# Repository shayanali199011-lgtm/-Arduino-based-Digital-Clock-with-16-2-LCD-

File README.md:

# -Arduino-based-Digital-Clock-with-16-2-LCD-
This project demonstrates how to design a basic Arduino Uno circuit in Eagle and program it to work as a digital clock. The time (hour:minute) is displayed on a 16×2 LCD. Users can set the time using push buttons.

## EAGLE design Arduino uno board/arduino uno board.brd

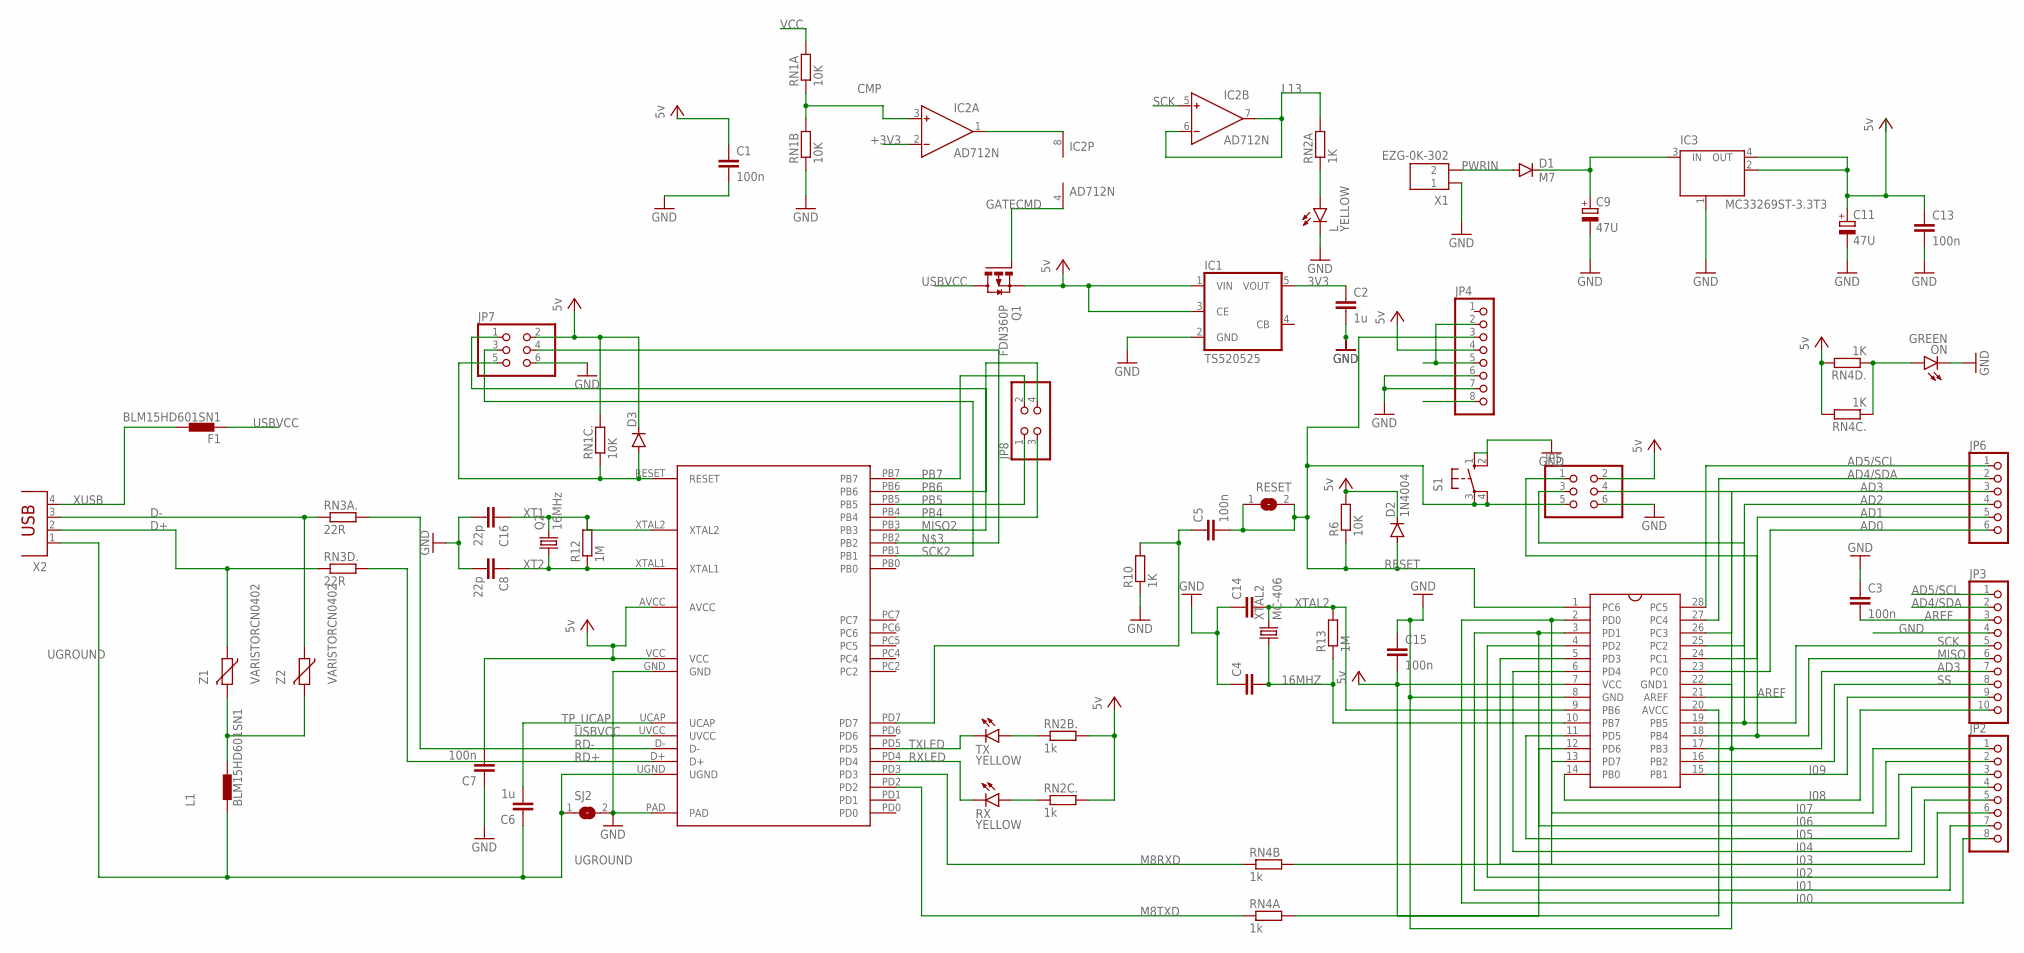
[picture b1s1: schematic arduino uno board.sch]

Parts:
C1, C3, C5, C7, C13, C15: 100n; C0603
C2, C6: 1u; C0603
C4, C14: C-EUC0603; C0603
C8, C16: 22p; C0603
C9, C11: 47U; R/2012-12W
D1: M7; MICROMELF-R
D2: 1N4004; MICROMELF-R
D3: DIODE-MICROMELF-R; MICROMELF-R
F1: BLM15HD601SN1; 0402
IC1: TS520525; SOT25
IC2: AD712N; DIL08
IC3: MC33269ST-3.3T3; SOT223
JP2, JP4: PINHD-1X8; 1X08
JP3: PINHD-1X10; 1X10
JP5, JP7: PINHD-2X3; 2X03
JP6: PINHD-1X6; 1X06
JP8: PINHD-2X2; 2X02
L: YELLOW; CHIPLED-0603-TTW
L1: BLM15HD601SN1; 0402
ON: GREEN; CHIPLED-0603-TTW
Q1: FDN360P; SUPER-SOT3
Q2: 16MHz; CTS406
R6: 10K; R0201
R10: 1K; R0201
R12, R13: 1M; R0201
RESET: SJ
RN1A, RN1B, RN1C.: 10K; R0201
RN2A, RN4C., RN4D.: 1K; R0201
RN2B., RN2C., RN4A, RN4B: 1k; R0201
RN3A., RN3D.: 22R; R0201
RX: YELLOW; CHIPLED-0603-TTW
S1: 10-XX; B3F-10XX
SJ2: SJ
TX: YELLOW; CHIPLED-0603-TTW
U$1: ARDUINOUNO
U$2: ATMEGA16U2
X1: EZG-0K-302; EZG-0B-0K-302
X2: PN61729
XTAL2: MC-406
Z1, Z2: VARISTORCN0402; CT/CN0402

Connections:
3V3: C2.1, IC1.5 (VOUT)
16MHZ: C4.2, R13.1, U$1.10 (PB7), XTAL2.1
+3V3: IC2.2 (IN-)
AD0: JP6.6, U$1.23 (PC0)
AD1: JP6.5, U$1.24 (PC1)
AD2: JP6.4, U$1.25 (PC2)
AD3: JP3.7, JP5.4, JP6.3, U$1.17 (PB3), U$1.26 (PC3)
AD4/SDA: JP3.2, JP6.2, U$1.27 (PC4)
AD5/SCL: JP3.1, JP6.1, U$1.28 (PC5)
AREF: C3.2, JP3.3, U$1.21 (AREF)
CMP: IC2.3 (IN+), RN1A.1, RN1B.2
D+: RN3D..1, X2.2, Z1.1
D-: RN3A..1, X2.3, Z2.1
GATECMD: IC2.4 (V-), Q1.1 (G)
GND: C1.2, C2.2, C3.1, C4.1, C7.1, C8.2, C9.-, C11.-, C13.2, C14.1, C15.1, C16.2, IC1.2 (GND), IC3.1 (GND/ADJ), JP3.4, JP4.6, JP4.7, JP5.6, JP7.6, L.C@1 (C), ON.C@1 (C), R10.1, RN1B.1, S1.1 (S), S1.2 (S1), SJ2.2, U$1.8 (GND), U$1.22 (GND1), U$2.GND, U$2.PAD, X1.1
I00: JP2.8, RN4B.2, U$1.2 (PD0)
I01: JP2.7, RN4A.2, U$1.3 (PD1)
I02: JP2.6, U$1.4 (PD2)
I03: JP2.5, U$1.5 (PD3)
I04: JP2.4, U$1.6 (PD4)
I05: JP2.3, U$1.11 (PD5)
I06: JP2.2, U$1.12 (PD6)
I07: JP2.1, U$1.13 (PD7)
I08: JP3.10, U$1.14 (PB0)
I09: JP3.9, U$1.15 (PB1)
L13: IC2.6 (IN-), IC2.7 (OUT), RN2A.2
M8RXD: RN4B.1, U$2.PD3
M8TXD: RN4A.1, U$2.PD2
MISO: JP3.6, JP5.1, U$1.18 (PB4)
MISO2: JP7.1, U$2.PB3
unnamed: RN2B..1, TX.A@1 (A)
unnamed: RN2C..1, RX.A@1 (A)
unnamed: JP7.4, U$2.PB2
unnamed: IC2.1 (OUT), IC2.8 (V+)
unnamed: C9.+, D1.C, IC3.3 (IN)
unnamed: L.A@1 (A), RN2A.1
unnamed: ON.A@1 (A), RN4C..1, RN4D..1
unnamed: C5.1, R10.2, U$2.PD7
unnamed: JP4.2, JP4.5
unnamed: D3.A, JP7.5, RN1C..1, U$2.RESET
unnamed: L1.2, Z1.2, Z2.2
PB4: JP8.3, U$2.PB4
PB5: JP8.1, U$2.PB5
PB6: JP8.4, U$2.PB6
PB7: JP8.2, U$2.PB7
PWRIN: D1.A, X1.2
RD+: RN3D..2, U$2.D+
RD-: RN3A..2, U$2.D-
RESET: C5.2, D2.A, JP4.3, JP5.5, R6.1, RESET.1, RESET.2, S1.3, S1.4 (P1), U$1.1 (PC6)
RXLED: RX.C@1 (C), U$2.PD4
SCK: IC2.5 (IN+), JP3.5, JP5.3, U$1.19 (PB5)
SCK2: JP7.3, U$2.PB1
SS: JP3.8, U$1.16 (PB2)
TP_UCAP: C6.2, U$2.UCAP
TXLED: TX.C@1 (C), U$2.PD5
UGROUND: C6.1, L1.1, SJ2.1, U$2.UGND, X2.1
USBVCC: F1.1, Q1.3 (D), U$2.UVCC
VCC: C1.1, C7.2, C11.+, C13.1, C15.2, D2.C, D3.C, IC1.1 (VIN), IC1.3 (CE), IC3.2 (OUT), IC3.4 (OUT), JP4.4, JP5.2, JP7.2, Q1.2 (S), R6.2, RN1A.2, RN1C..2, RN2B..2, RN2C..2, RN4C..2, RN4D..2, U$1.7 (VCC), U$1.20 (AVCC), U$2.AVCC, U$2.VCC
XT1: C16.1, Q2.3 (2), R12.2, U$2.XTAL2
XT2: C8.1, Q2.1, R12.1, U$2.XTAL1
XTAL2: C14.2, R13.2, U$1.9 (PB6), XTAL2.4 (2)
XUSB: F1.2, X2.4

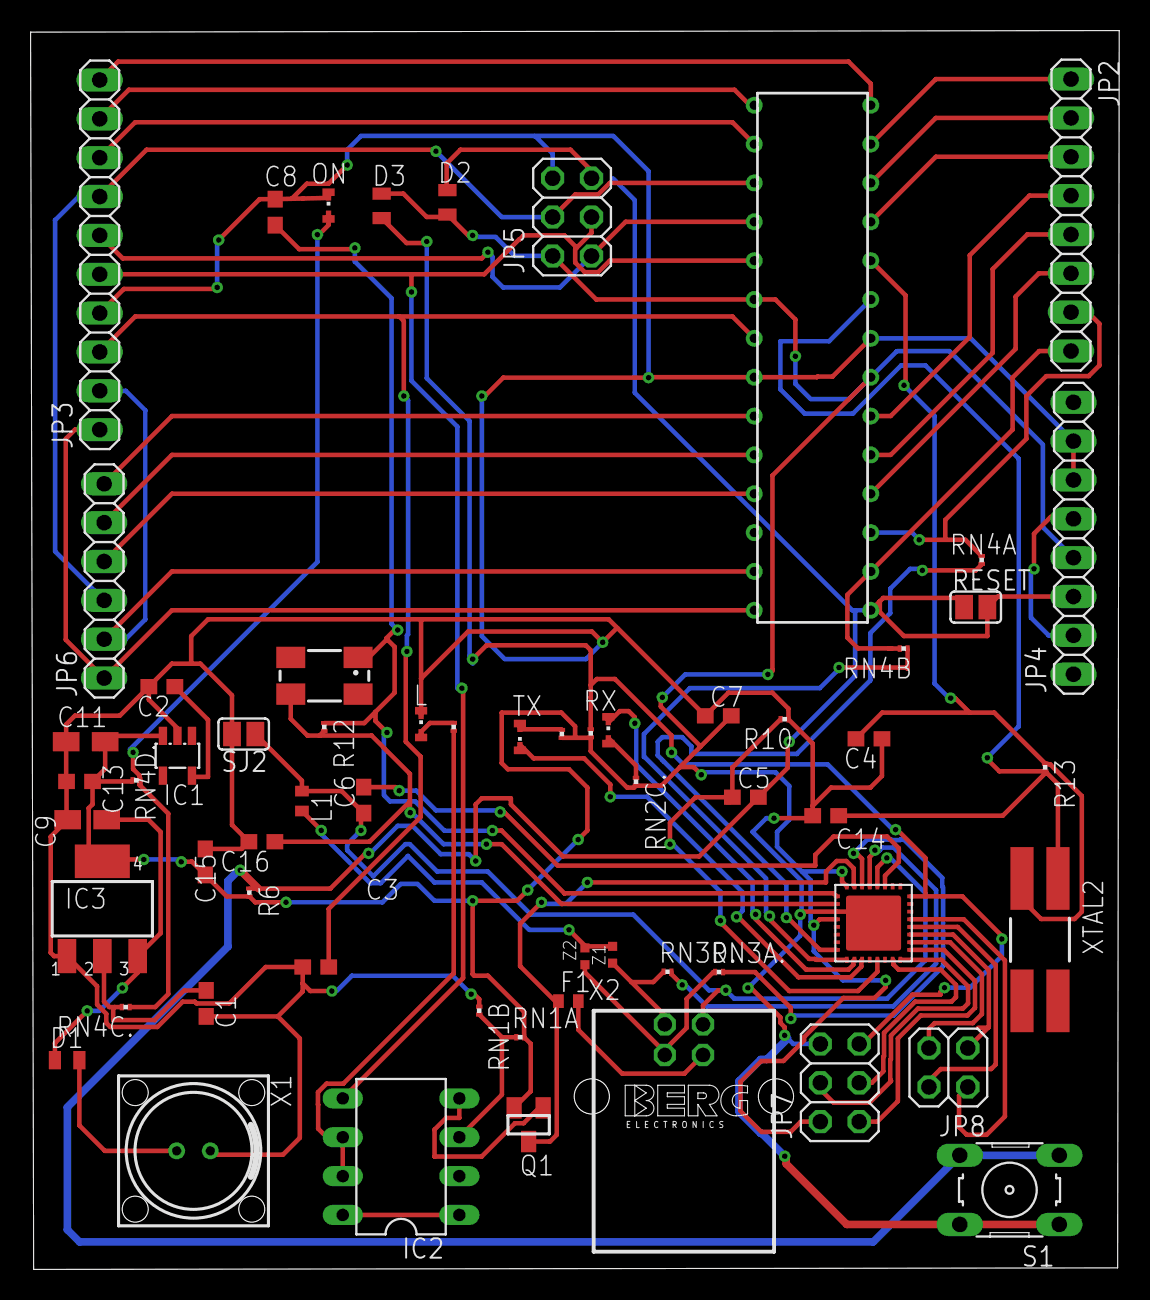
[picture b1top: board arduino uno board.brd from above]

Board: 2 copper layers, 71.2 x 81.0 mm, 61 parts (0 on the bottom side), 61 nets.

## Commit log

2025-09-21 Add files via upload
    Features:
    Custom Arduino Uno board design created in Eagle CAD
    16×2 LCD for displaying time
    Three push buttons for setting hour, minute, and toggling display
    Simple Arduino code to keep and update time
    Hardware Used:
